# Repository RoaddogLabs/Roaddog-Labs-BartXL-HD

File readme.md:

## Roaddog Labs Bart Pro XL
## 
This is the Roaddog Bart XL 3D printer. This machine is a larger build
based on a mashup implemented from several designs including original
designs.  

####This machine is available in two variants

#####Bart Pro XL-LC is a lower cost version and a good upgrade platform for those with a Prusa i3 or Rework i3 variant to upgrade to a better frame and larger build area.  The LC variant uses M8 X and Z smooth rods and M5 threaded rod for the Z drive screw.  The LC uses Rework i3 printed parts.

The Bart Pro XL-LC version is frozen.  The current version is the Bart Pro XL-HD.  There will be no more work on this version but feel free to fork it and do with it as you wish.

#####Bart Pro XL-HD uses high performance lead screws, M10 precision shaft on all axis, high temp hot end suitable to 400*C, auto bed probe (bed leveling), silcone bed heater, MIC 6 precision aluminum print surface with PEI.

### This is a pre release version
### 
The current version is a pre release.  While the machine is functional
and works well, it's still very much a work in progress.  A set of pre release docs are at http://roaddoglabs.io/wiki/Roaddog_Labs_Bart_Pro_XL

Pull requests are welcome and encouraged.

#### Roaddog Labs Bart Pro XL-HD Specs ####

| Feature | Bart Pro XL-HD |
|---------|-------------|
| Base and Frame | Full melamine frame, printed parts, latest design for maximum stability and print speeds |
| Build Envelope | 360 mm x 240 mm x 200 mm |
| Resolution (printable layer thickness) | low res .3 mm; normal res .2 mm; hi res .1 mm; extra hi res .06 mm |
| Filament Diameter | 1.75 |
| Max Printing Temp | 248&#176; C with E3D Lite v6; 300&#176; C with E3D full v6 with thermistor, 400&#176; C with optional thermocouple |
| Compatible Materials | With E3D v6, any printable material to 400&#176; C with E3D v6 and thermocouple.  With E3D Lite v6 more than 15 types including PLA, ABS, Laywoo-D, HIPS, carbon fiber reinforced PLA, flexible filament, conductive PLA |
| Nozzle Size | .4 mm standard, user upgradable to a variety of sizes |
| Heated Bed | Polyimide heater, 24 volt with aluminum heat spreader |
| Print Surface |0.125" 6061-T6 aluminum |
| Extruder | Bart Direct Drive MK7, low profile, reduced weight and mass, optional E3D Titan or Bondtech QR extruder |
| Bed Tilt Compensation | Belt tilt compensation, also called auto bed leveling or tramming via an inductive sensor |
|Electronics | Mini Rambo configured for Bart Pro XL with Marlin firmware |
| Power Supply | 24 volts, 400 watts compact form factor |
| X Axis Motion | GT2 belt and pulley;  10 mm precision  bearings and chromed, hardened rods |
| Y Axis Motion | GT2 belt and pulley;  10 mm precision  bearings and chromed, hardened rods |
| Z Axis Motion | TR8 precision lead screw and nut; 10 mm precision bearings and chromed, hardened rods |
| Average Speeds | 100 mm/s (stock extruder, perimeters based on average tune) |
| Machine Footprint | 512 mm x 470 mm x 400 mm |
| Display/SD Card Reader | Full graphic LCD display and SD card reader for standalone operation |
| Optional Wireless and Print Server | User installed optional printing over Wifi and dedicated print server using Octoprint and a Raspberry Pi |

####License and Credits

Original designs from Roaddog Labs Ltd are released per the
Open Source Hardware Association guidelines for open source hardware at
http://www.oshwa.org/definition/.

Material specific to the Bart components and documentation that is not
derived from other sources are released under the Creative Commons
Attribution 4.0 International license.

Where applicable, the license of any derived work will be posted as
well.

The original Prusa i3 single plate files
(https://github.com/josefprusa/Prusa3) from Josef Prusa licensed under
GPL v3.

The original i3 Rework
(https://github.com/eMotion-Tech/Prusai3_EINSTEIN_Reworked) printed
parts files from eMotion-Tech are released under GPL 2.0.

The original i3 Hephestos files
(https://github.com/bq/prusa-i3-hephestos/) from bq Department of
Innovation and Robotics are licensed under Creative Commons Attribution
4.0 Sharealike International.

The Graber i3(https://github.com/sgraber/Graber) is licensed under GPL
v3.0.

The original modified i3 X idler with adjustable belt tensioner from
ramkam (http://www.thingiverse.com/thing:393870) licensed under Creative
Commons Atribution-Sharealike, no version stated.

Marlin firmware (https://github.com/MarlinFirmware/Marlin) from Erik van
der Zalm licensed under GPL, no version stated.

The original direct drive extruder for Wilson/i3
(http://www.thingiverse.com/thing:501755) from mrice licensed under
Creative Commons Attribution- Share Alike license, no version stated.

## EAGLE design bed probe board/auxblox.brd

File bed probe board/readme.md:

This is the voltage divider circuit and board layout for the Roaddog Labs Bart Pro XL.  It takes a 24 volt input and reduces the switch output to 5 volts for triggering the MCU on the printer.

This is pre release, not for production.

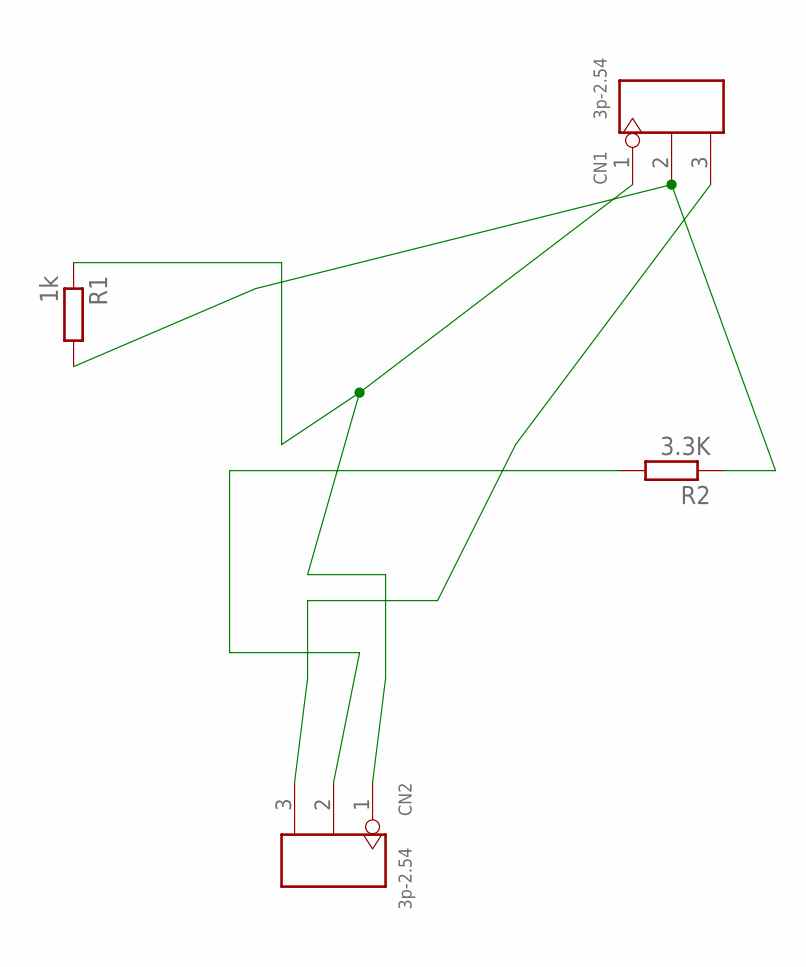
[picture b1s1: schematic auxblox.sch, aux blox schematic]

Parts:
CN1, CN2: 3p-2.54; H3-2.54
R1: 1k; R0805
R2: 3.3K; R0805

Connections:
unnamed: CN1.3, CN2.3
unnamed: CN2.2, R2.2
unnamed: CN1.1, CN2.1, R1.1
unnamed: CN1.2, R1.2, R2.1

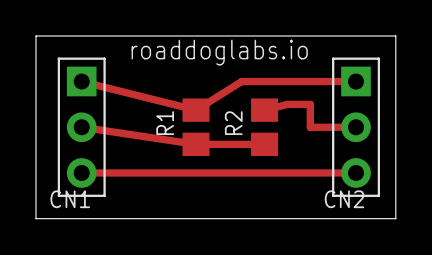
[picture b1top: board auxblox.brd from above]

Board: 2 copper layers, 20.0 x 10.1 mm, 4 parts (0 on the bottom side), 4 nets.

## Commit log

2015-09-11 initial commit
    initial commit
2015-09-11 add gitignore
2015-10-24 working proto
    woring prototype with dual extruder carriage
2015-10-24 base dual extruder Marlin config
    add base dual marlin config with larger build envelope and activated
    watchdog
2015-10-24 bed revision
    added print plate mounting holes
    extended endstop trigger
2015-10-24 added extra cut parts, new top
2015-10-24 file clean up
2015-11-08 update frame parts
    update to “pro” frame, taller, more stable
2015-12-08 update Marlin RAMPS to Bart XL
2015-12-08 update bed frame to LM10uu
2015-12-08 update Marlin 1.1.0-RC2 config & add RC3 dist
2015-12-08 update bom lm10uu parts difference
2015-12-25 Use Prusa's Marlin 1.0.3 for Mini Rambo
    rolled back to a build-able version of Marlin
    removed the two 1.1 RC branches
2015-12-25 archive v1 base part
2015-12-25 update printed parts and source
2015-12-25 set base firmware config
2015-12-25 edit pins.h to fix max end stops
2015-12-25 adjust motor current
2016-01-10 update firmware config
2016-01-10 dual extruder x carriage updates
2016-02-06 release candidate firmware
    archive older versions to folder
    implement Marlin 1.1.0 RC3
2016-02-13 update bom for lm10 mounts
2016-02-13 revise source attributions and credits
2016-02-13 removed unused frame files
2016-02-13 remove corel files
2016-02-13 firmware config update
2016-02-13 add lm10 Y bearing mounts
2016-02-18 config for ambit
2016-02-18 lm10 x carriage
2016-02-18 m10 x axis
2016-02-19 update frame base for Y endstop bracket
2016-02-25 update Y motor mount
2016-03-10 widen main frame
    widen main frame, still needs Z travel confirmed
2016-03-10 update .git ignore for owl and dwell files
2016-03-13 fixed X idler file name
2016-03-16 mod for 2 hole y clip
    2 hole y clip for 10 mm y rods also mod ends
2016-03-16 update Y motor mount
    fixed nut trap sizes, made main body thicker, added fillets
2016-03-19 add glad case
2016-03-19 update z top for wider frame
2016-03-19 update print bed
2016-03-19 remove old parts files
2016-03-19 update to y clip
2016-03-19 update x axis lm10uu parts
    added no zip tie x carriage
    mod to motor end and idler end
2016-03-19 remove lm8 y axis holders
2016-03-20 update firmware read
2016-03-20 update config for Mini Rambo
2016-03-20 clean out deprecated files
    get rid of .step, obj and dxf files from printed parts source dir
2016-03-20 update read
2016-03-22 add y idler
2016-03-22 un nest z frame
    removed the z top and other z parts from the drawing to their own
    drawings
2016-03-28 bed probe circuit
    voltage divider for bed probe circuit 24 volts to 5 volts
2016-03-28 bed probe bracket v1
    stl and source for bed probe bracket
2016-04-03 adjust motor pwm
    changed motor driver current settings to approx .75 amps
2016-04-03 bed probe firmware settings
    changed settings for bed probe
    renamed file for mechanical z end stop
    updated readme
2016-04-03 update firmware readme
2016-04-03 update y motor mount
    update nut traps
    update slots for belt adjustment
    thicker mount
2016-04-03 push 1st rev of 2nd gen extruder
    2nd gen extruder and idler stl and source
2016-04-03 update 2G ext readme
2016-04-05 update PID values for E3D 24 volt
2016-04-07 marlin 1.1.0-rc5
    easier to pull a new branch and merge my changes
2016-04-07 update README.md for RC5
2016-04-07 bart pro xl configs
    per normal the latest “release candidate” of marlin is broken and
    breaks things that have worked for years.
2016-04-09 config settings
    adjust bed probe distance
    disable bed runaway
2016-04-09 reduce jerk, change default pre heat temps
2016-04-11 add extruder with motor on right
2016-04-13 first draft titan carriage and bracket
2016-04-17 update titan x carriage and mount
    second prototype of both parts
2016-04-18 remove thermal settings
2016-04-18 add todo list
2016-04-18 update todo list
2016-04-24 add steps per mm for lead screws in firmware
2016-04-24 updated titan carriage and bracket
2016-04-24 1st rev of m10 z and lead screw parts
    1st rev of m10 z rods and m8 lead screws
    x motor end
    x idler end
    no x idler at this point
    removed older m8 rod parts
2016-04-24 remove v1 parts from repo
2016-04-24 add m10 z bottom rod guide
2016-04-24 2nd rev of 2nd gen extruder
    adjusted tensioner centerline
    slotted tensioner screw holes
    fixed e3d mount
2016-04-24 updated lead screw motor mounts
    adjusted spacing for z top and z motor mounts for m10 rods and lead
    screws
2016-04-24 add m10 rod and lead screw main plate
2016-04-26 refinements to 2nd gen extruder
    larger hot end mount hole
    changed alignment of idler bearing to hob
2016-04-26 refinements to m10 lead screw x parts
    strengthen x end stop mount
    thicker z bearing mount walls
    re profile x idler end
    addressed clearance issues with x idler
2016-04-26 move m8 parts to archive folder
2016-04-26 sync m10 file version of idler end
2016-05-22 parts updates for lead screw variant
2016-05-23 commit lc frame parts
2016-05-23 add lc readme
2016-05-23 commit lc printed parts
2016-05-23 commit lc z motor support
2016-05-23 add lc frame readme
2016-05-23 update frame readme
2016-05-23 commit lc y motor mount
2016-05-23 add printed parts readme
2016-05-23 add lc bom
2016-05-23 edit lc bom
2016-06-09 change resistors to 0805 package
    changed package on r1 and r2, update mom and berbers
2016-07-27 update lc mom
